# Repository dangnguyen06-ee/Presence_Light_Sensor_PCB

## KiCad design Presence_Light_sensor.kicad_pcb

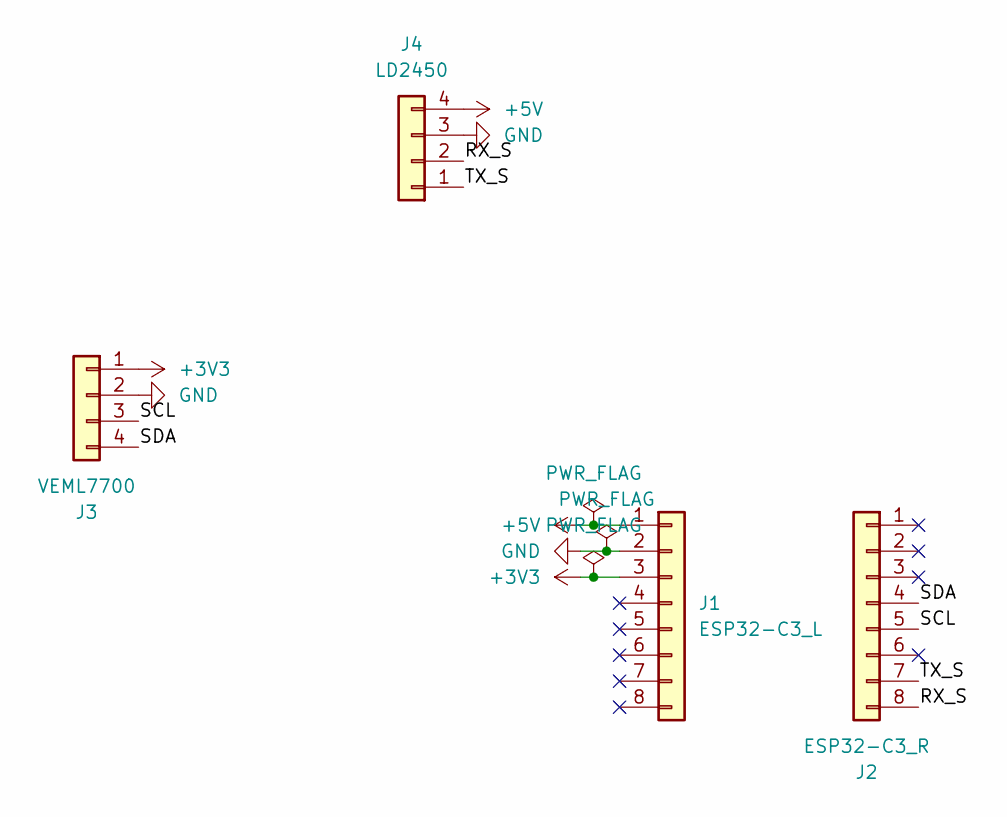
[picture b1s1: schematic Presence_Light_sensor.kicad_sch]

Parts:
J1: ESP32-C3_L; PinSocket_1x08_P2.54mm_Vertical
J2: ESP32-C3_R; PinSocket_1x08_P2.54mm_Vertical
J3: VEML7700; PinSocket_1x04_P2.54mm_Vertical
J4: LD2450; PinSocket_1x04_P2.54mm_Vertical

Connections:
+3V3: J1.3, J3.1
+5V: J1.1, J4.4
/RX_S: J2.8, J4.2
/SCL: J2.5, J3.3
/SDA: J2.4, J3.4
/TX_S: J2.7, J4.1
GND: J1.2, J3.2, J4.3

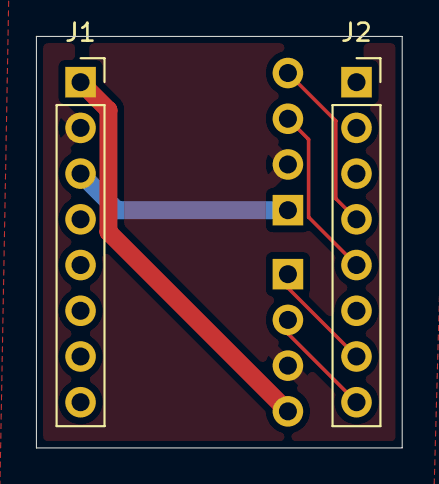
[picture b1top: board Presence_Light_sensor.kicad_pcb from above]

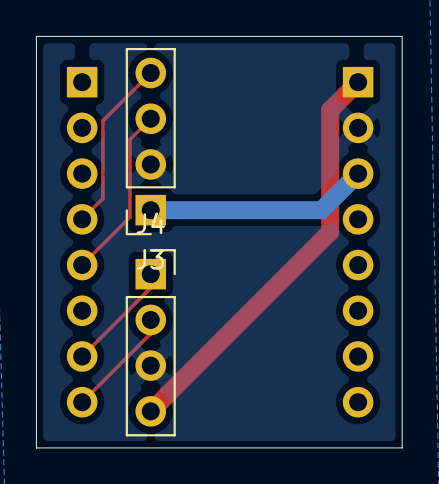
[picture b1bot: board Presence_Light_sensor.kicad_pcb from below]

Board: 2 copper layers, 20.3 x 22.9 mm, 4 parts (2 on the bottom side), 7 nets.
